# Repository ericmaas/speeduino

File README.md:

## NO2C vDD

All Credit to the Speeduino Team
https://github.com/speeduino/speeduino

And 

https://github.com/turboedge/SpeedyBoards/

Originally forked from:
https://github.com/turboedge/SpeedyBoards/tree/master

Wideband ideation from:
https://github.com/oelprinz-org

Please review my workprior to printing, and test your work. 

I am not an engineer, mechanic, or automotive specialist, please use at your own risk.

Please review vehicle laws and regulations prior to use. 

Connector used is a TE # 3-6437285-0

Future Feature Wish List:

- SD Card for data logging
- Dedicated prototyping pins (would be great for oil pressure)

The No Overhang Two Channel was designed to incorporate as many features as possible into a SMD board that moves to a new smaller format size. Microcontroller onboard. It is a 2+2 channel board that incorporates the features below.
- Two injector channels
- Two ignitor channels
- Outputs for VVT PWM idle, boost, fuel pump, and tachometer
- Two trigger inputs
- Launch input
- Analog inputs for CLT, IAT, TPS, and O2
- MAP sensor onboard
- Socket for stepper idle control module
- Additional pins for i2c and canbus
- LSU 4.9 Wideband integration
- Bluetooth 4.0 (HM-10)

Latest version: DD3

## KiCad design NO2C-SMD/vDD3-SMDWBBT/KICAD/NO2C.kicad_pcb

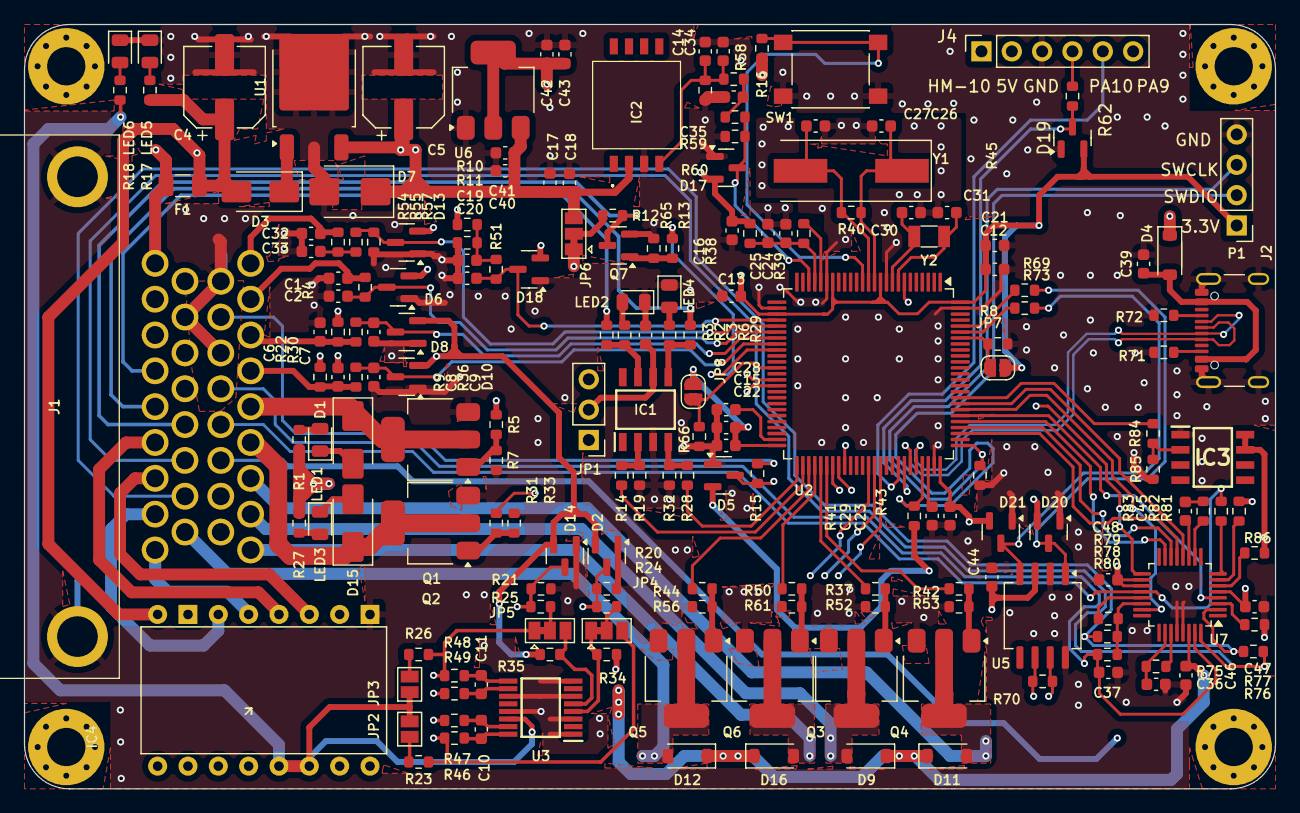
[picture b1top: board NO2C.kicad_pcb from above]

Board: 4 copper layers, 104.8 x 64.0 mm, 188 parts (0 on the bottom side), 136 nets.

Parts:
C1, C3, C6, C8, C13, C15, C16, C17, C18, C19, C21, C22, C23, C25, C28, C29, C32, C34, C36, C40, C43, C44, C45, C46, C47, C48: 100nF; C_0603_1608Metric
C2, C7, C9, C20, C33, C35: 220nF; C_0603_1608Metric
C4, C5: 47u 50v; CP_Elec_6.3x7.7
C10, C11, C12, C24: 1nF; C_0603_1608Metric
C14: 47pF; C_0603_1608Metric
C26, C27: 22pF; C_0603_1608Metric
C30, C31: 12pF; C_0603_1608Metric
C37: 2.2nF; C_0603_1608Metric
C39, C41, C42: 10uF; C_0603_1608Metric
D1, D15: 1N4004; D_SMA
D2, D5, D6, D8, D10, D13, D14, D17, D18, D19, D20, D21: BAT54S; SOT-23
D3: 60V 1A; D_SMA
D4, D9, D11, D12, D16: 1N4007-A7; D_SOD-123
D7: 1SMB5919BT3G; D_SMB
F1: 1A 60V; Fuse_1206_3216Metric
IC1: TC4424AVOA; SOIC127P600X175-8N
IC2: MPXH6400AC6T1
IC3: VNS3NV04DPTR-E; SOIC127P600X175-8N
IC4: CONN_02X08; DRV8825
J1: 3-6437285-0; 364372850
J2: USB_C_Receptacle_USB2.0_16P; USB_C_Receptacle_GCT_USB4105-xx-A_16P_TopMnt_Horizontal
J4: HM-10; PinSocket_1x06_P2.54mm_Vertical
JP1: ING-VLT; PinHeader_1x03_P2.54mm_Vertical
JP2, JP3: Jumper_NO_Small; SolderJumper-2_P1.3mm_Open_Pad1.0x1.5mm
JP4, JP5, JP6: SolderJumper_3_Bridged12; SolderJumper-3_P1.3mm_Bridged12_Pad1.0x1.5mm
JP7, JP8: Jumper_2_Open; SolderJumper-2_P1.3mm_Open_RoundedPad1.0x1.5mm
LED1, LED2, LED3, LED4, LED5, LED6: RED; LED_0805_2012Metric
P1: Conn_01x04; PinHeader_1x04_P2.54mm_Vertical
Q1, Q2, Q3, Q4, Q5, Q6: BSP78HUMA1; SOT-223-3_TabPin2
Q7: AO3400A; SOT-23
R1, R2, R6, R27: 2K; R_0603_1608Metric
R3, R29: 47R; R_0603_1608Metric
R4, R18, R24, R25, R30, R36, R51, R54, R58, R62: 470R; R_0603_1608Metric
R5, R13, R31, R37, R42, R44, R50: 100R; R_0603_1608Metric
R7, R8, R16, R20, R21, R33, R41, R43, R46, R47, R48, R49, R52, R53, R56, R61, R65, R66, R77, R81, R82, R83: 10K; R_0603_1608Metric
R9, R22: 2K49; R_0603_1608Metric
R10: 33K; R_0603_1608Metric
R11, R45: 51K; R_0603_1608Metric
R12, R14, R15, R23, R26, R28, R34, R35, R69, R73: 1K; R_0603_1608Metric
R17: 2K7; R_0603_1608Metric
R19, R32, R75, R80, R85: 100K; R_0603_1608Metric
R38, R39: 0R; R_0603_1608Metric
R40: 1M; R_0603_1608Metric
R55, R59: 4K7; R_0603_1608Metric
R57, R60: 9K1; R_0603_1608Metric
R70: 120R; R_0603_1608Metric
R71, R72: 5.1K; R_0603_1608Metric
R76: 61.9R; R_0603_1608Metric
R78: 470K; R_0603_1608Metric
R79, R84: 4.7K; R_0603_1608Metric
R86: 6.8K; R_0603_1608Metric
SW1: SW_Push; SW_Push_1P1T_NO_6x6mm_H9.5mm
U1: L7805CDT(UMW); TO-252-2
U2: STM32F407VETx; LQFP-100_14x14mm_P0.5mm
U3: MAX9926UAEE+; SOP64P602X175-16N
U5: TJA1050; SO-8_5.3x6.2mm_P1.27mm
U6: AMS1117-3.3; SOT-223-3_TabPin2
U7: CJ125_32; LQFP-32_5x5mm_P0.5mm
Y1: 8Mhz; Crystal_SMD_HC49-SD
Y2: 32.768Khz; Crystal_SMD_3215-2Pin_3.2x1.5mm

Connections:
+3.3V: C12.2, C13.2, C15.2, C16.2, C21.2, C22.2, C23.2, C42.1, C43.1, D2.2 (C2), D5.2 (K), D6.2 (K), D8.2 (K), D10.2 (K), D13.2 (K), D14.2 (C2), D17.2 (K), D18.2 (K), D19.2 (K), D20.2 (K), D21.2 (K), JP7.2 (B), JP8.2 (B), P1.1, R9.1, R16.1, R22.1, R34.2, R35.2, R38.2, R41.1, U2.11 (VDD), U2.19 (VDD), U2.28 (VDD), U2.50 (VDD), U2.75 (VDD), U2.100 (VDD), U6.2 (VO)
+5V: C5.1, C17.1, C18.1, C40.1, C41.1, C44.1, C47.2, C48.2, D4.1 (K), D7.1 (K), IC2.2 (_VS), IC4.5, IC4.6, J1.10, J4.2, JP1.1, JP2.2, JP3.2, JP6.3 (B), R18.1, R81.1, U1.3 (OUT), U3.14 (VCC), U5.3 (vcc), U6.3 (VI), U7.5 (VCCS), U7.18 (VCCSS), U7.19 (VCC)
+12V: C4.1, C46.2, D3.2 (A), D9.1 (K), D11.1 (K), D12.1 (K), D16.1 (K), F1.1, IC4.16, JP1.3, JP6.1 (A), R1.2, R17.2, R27.2, U7.30 (UB)
+BATT: F1.2, J1.1, R10.1
/BOOST: D9.2 (A), J1.33, Q3.2 (D)
/BOOT0: JP7.1 (A), R8.2, U2.94 (BOOT0)
/BOOT1: JP8.1 (A), R66.1, U2.37 (PB2)
/CLT: C6.1, J1.28, R22.2, R30.1
/DIAHG: U2.81 (PD0), U7.4 (DIAHG)
/DIR: IC4.8, U2.65 (PC8)
/ENBL: IC4.1, U2.63 (PC6)
/FUELP: D16.2 (A), J1.34, Q6.2 (D)
/HEAT_OUT-: R84.1, U2.84 (PD3)
/IAT: C8.1, J1.29, R9.2, R36.1
/IDLE: D12.2 (A), J1.17, Q5.2 (D)
/IGN1: J1.4, R3.2
/IGN2: J1.5, R29.2
/INJ1: D1.1 (K), J1.30, Q1.2 (D)
/INJ2: D15.1 (K), J1.31, Q2.2 (D)
/LAUNCH: J1.19, R15.2
/O2: C32.1, J1.26, R54.1
/PA0: D17.3 (COM), R59.2, R60.2, U2.23 (PA0)
/PA1: C20.1, D18.3 (COM), R51.2, U2.29 (PA4)
/PA2: D13.3 (COM), R55.2, R57.2, U2.30 (PA5)
/PA3: C2.1, D6.3 (COM), R4.2, U2.31 (PA6)
/PA4: C7.1, D8.3 (COM), R30.2, U2.32 (PA7)
/PA5: C9.1, D10.3 (COM), R36.2, U2.33 (PC4)
/PA9: J4.5, U2.68 (PA9)
/PA10: D19.3 (COM), R62.1, U2.69 (PA10)
/PB8: R73.1, U2.95 (PB8)
/PB9: R69.1, U2.96 (PB9)
/PD4: R50.2, U2.54 (PB15)
/PD5: R44.2, U2.53 (PB14)
/PD6: R42.2, U2.56 (PD9)
/PD7: R37.2, U2.55 (PD8)
/PD8: R5.2, U2.39 (PE8)
/PD9: R31.2, U2.40 (PE9)
/PD10: D14.3 (C1A2), R21.1, R25.1, U2.57 (PD10)
/PD11: D2.3 (C1A2), R20.1, R24.1, U2.58 (PD11)
/PD12: R28.2, U2.51 (PB12)
/PD13: R14.2, U2.52 (PB13)
/PD14: R13.1, U2.34 (PC5)
/SPI3_MISO: U2.79 (PC11), U7.14 (MISO)
/SPI3_MOSI: U2.80 (PC12), U7.15 (MOSI)
/SPI3_SCK: U2.78 (PC10), U7.13 (SCK)
/SS3: U2.7 (PC13), U7.17 (SS)
/STEP: IC4.7, U2.64 (PC7)
/STP-A1: IC4.12, J1.6
/STP-A2: IC4.11, J1.7
/STP-B1: IC4.13, J1.9
/STP-B2: IC4.14, J1.8
/SWCLK: P1.3, R43.1, U2.76 (PA14)
/SWDIO: P1.2, R41.2, U2.72 (PA13)
/TACHO: J1.14, Q7.3 (D), R12.1
/TPS: C1.1, J1.27, R4.1
/UA: U2.82 (PD1), U7.23 (UA)
/UR: U2.83 (PD2), U7.12 (UR)
/USB_D+: J2.A6 (D+), J2.B6 (D+), U2.71 (PA12)
/USB_D-: J2.A7 (D-), J2.B7 (D-), U2.70 (PA11)
/VR1-: J1.3, R47.1
/VR2-: J1.12, R49.1
/VVT: D11.2 (A), J1.32, Q4.2 (D)
CANH: J1.24, R70.2, U5.7 (CANH)
CANL: J1.25, R70.1, U5.6 (CANL)
DIAHD: R86.1, U7.6 (DIAHD)
GND: C1.2, C2.2, C3.2, C4.2, C5.2, C6.2, C7.2, C8.2, C9.2, C12.1, C13.1, C14.2, C15.1, C16.1, C17.2, C18.2, C19.2, C20.2, C21.1, C22.1, C23.1, C24.1, C25.1, C26.1, C27.1, C28.1, C29.1, C30.1, C31.1, C32.2, C33.2, C34.2, C35.2, C36.2, C37.1, C39.2, C40.2, C41.2, C42.2, C43.2, C44.2, C46.1, C47.1, C48.1, D2.1 (A1), D5.1 (A), D6.1 (A), D7.2 (A), D8.1 (A), D10.1 (A), D13.1 (A), D14.1 (A1), D17.1 (A), D18.1 (A), D19.1 (A), D20.1 (A), D21.1 (A), IC1.3 (GND), IC2.3 (GND), IC3.1 (SOURCE1), IC4.9, J1.11, J1.18, J1.20, J1.MH1, J1.MH2, J2.A1 (GND), J2.A12 (GND), J2.B1 (GND), J2.B12 (GND), J2.S1 (SHIELD), J4.3, LED2.1 (K), LED4.1 (K), LED5.1 (K), LED6.1 (K), P1.4, Q1.3 (S), Q2.3 (S), Q3.3 (S), Q4.3 (S), Q5.3 (S), Q6.3 (S), Q7.2 (S), R7.2, R8.1, R11.2, R19.2, R20.2, R21.2, R32.2, R33.2, R43.2, R45.2, R52.2, R53.2, R56.2, R57.1, R60.1, R61.2, R65.2, R66.2, R71.2, R72.2, R77.1, R85.1, SW1.1, U1.2 (GND), U2.10 (VSS), U2.20 (VSSA), U2.27 (VSS), U2.74 (VSS), U2.99 (VSS), U3.1 (INT_THRS1), U3.3 (BIAS1), U3.6 (BIAS2), U3.8 (INT_THRS2), U3.11 (GND), U3.13 (ZERO_EN), U5.2 (gnd), U5.8 (S), U6.1 (GND), U7.28 (GNDS), U7.29 (GND)
HEAT-: IC3.7 (DRAIN1_1), IC3.8 (DRAIN1_2), J1.23, R86.2
IA: J1.16, R76.1, R78.2, U7.2 (IA)
IP: J1.15, R76.2, U7.32 (IP)
unnamed: C19.1, R10.2, R11.1, R51.1
unnamed: C33.1, R54.2, R55.1
unnamed: C35.1, R58.2, R59.1
unnamed: C45.1, R83.2
unnamed: D1.2 (A), LED1.1 (K)
unnamed: D3.1 (K), U1.1 (IN)
unnamed: D5.3 (COM), R15.1, U2.59 (PD12)
unnamed: D15.2 (A), LED3.1 (K)
unnamed: D20.3 (COM), R69.2, U5.1 (txd)
unnamed: D21.3 (COM), R73.2, U5.4 (rxd)
unnamed: IC1.2 (INA), R14.1, R19.1
unnamed: IC1.4 (INB), R28.1, R32.1
unnamed: IC1.7 (OUTA), R2.1, R3.1
unnamed: IC1.5 (OUTB), R6.1, R29.1
unnamed: C3.1, IC1.6 (VDD), JP1.2
unnamed: C14.1, C34.1, IC2.4 (VOUT), R45.1, R58.1
unnamed: IC3.2 (INPUT_1), R84.2, R85.2
unnamed: J2.A8 (SBU1), R72.1
unnamed: J2.B8 (SBU2), R71.1
unnamed: J4.4, R62.2
unnamed: JP2.1, R23.2
unnamed: JP3.1, R26.2
unnamed: JP4.1 (A), R34.1, U3.4 (COUT1)
unnamed: JP4.2 (C), R24.2
unnamed: JP5.3 (B), R35.1, U3.5 (COUT2)
unnamed: JP5.2 (C), R25.2
unnamed: JP6.2 (C), R12.2
unnamed: LED1.2 (A), R1.1
unnamed: LED2.2 (A), R2.2
unnamed: LED3.2 (A), R27.1
unnamed: LED4.2 (A), R6.2
unnamed: LED5.2 (A), R17.1
unnamed: LED6.2 (A), R18.2
unnamed: Q1.1 (G), R5.1, R7.1
unnamed: Q2.1 (G), R31.1, R33.1
unnamed: Q3.1 (G), R37.1, R52.1
unnamed: Q4.1 (G), R42.1, R53.1
unnamed: Q5.1 (G), R44.1, R56.1
unnamed: Q6.1 (G), R50.1, R61.1
unnamed: Q7.1 (G), R13.2, R65.1
unnamed: R16.2, SW1.2, U2.14 (NRST)
unnamed: C31.2, U2.8 (PC14), Y2.2
unnamed: C30.2, U2.9 (PC15), Y2.1
unnamed: C26.2, R40.1, U2.12 (PH0), Y1.1
unnamed: C27.2, R40.2, U2.13 (PH1), Y1.2
unnamed: C28.2, U2.49 (VCAP_1)
unnamed: C29.2, U2.73 (VCAP_2)
unnamed: R39.2, U2.21 (VREF+)
unnamed: C10.2, R46.2, U3.16 (IN1+)
unnamed: C10.1, R47.2, U3.15 (IN1-)
unnamed: C11.2, R48.2, U3.9 (IN2+)
unnamed: C11.1, R49.2, U3.10 (IN2-)
unnamed: C36.1, R75.2, U7.26 (CF)
unnamed: C45.2, U7.11 (CM)
unnamed: R77.2, U7.3 (OSZ)
unnamed: R75.1, U7.27 (RF)
unnamed: R83.1, U7.10 (RM)
unnamed: R82.2, U7.8 (RS)
unnamed: R81.2, U7.7 (RST)
unnamed: R78.1, R79.2, R80.1, U7.22 (UP)
unnamed: R79.1, U7.21 (US)
UN: C37.2, J1.21, R80.2, U7.31 (UN)
VBUS: C39.1, D4.2 (A), J2.A4 (VBUS), J2.A9 (VBUS), J2.B4 (VBUS), J2.B9 (VBUS)
VDA: C24.2, C25.2, R38.1, R39.1, U2.22 (VDDA)
VM: J1.22, R82.1, U7.20 (VM)
VR1+: J1.2, JP4.3 (B), R23.1, R46.1
VR2+: J1.13, JP5.1 (A), R26.1, R48.1

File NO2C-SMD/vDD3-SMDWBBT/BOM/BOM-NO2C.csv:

Comment,Designator,Footprint,LCSC,Quantity
22pF,"C26,C27",C_0603_1608Metric,C105620,2
47pF,C14,C_0603_1608Metric,C105622,1
12pF,"C30,C31",C_0603_1608Metric,C107034,2
220nF,"C2,C20,C33,C35,C7,C9",C_0603_1608Metric,C107083,6
10uF,"C39,C41,C42",C_0603_1608Metric,C109457,3
8Mhz,Y1,Crystal_SMD_HC49-SD,C12674,1
2K7,R17,R_0603_1608Metric,C13167,1
60V 1A,D3,D_SMA,C134421,1
100nF,"C1,C13,C15,C16,C17,C18,C19,C21,C22,C23,C25,C28,C29,C3,C32,C34,C36,C40,C43,C44,C45,C46,C47,C48,C6,C8",C_0603_1608Metric,C14663,26
MAX9926UAEE+,U3,SOP64P602X175-16N,C1523548,1
1A 60V,F1,Fuse_1206_3216Metric,C163133,1
1nF,"C10,C11,C12,C24",C_0603_1608Metric,C1636,4
USB_C_Receptacle_USB2.0_16P,J2,USB_C_Receptacle_GCT_USB4105-xx-A_16P_TopMnt_Horizontal,C165948,1
CJ125_32,U7,LQFP-32_5x5mm_P0.5mm,C18198890,1
0R,"R38,R39",R_0603_1608Metric,C21189,2
1K,"R12,R14,R15,R23,R26,R28,R34,R35,R69,R73",R_0603_1608Metric,C21190,10
100R,"R13,R31,R37,R42,R44,R5,R50",R_0603_1608Metric,C22775,7
120R,R70,R_0603_1608Metric,C22787,1
2K49,"R22,R9",R_0603_1608Metric,C22908,2
1M,R40,R_0603_1608Metric,C22935,1
2K,"R1,R2,R27,R6",R_0603_1608Metric,C22975,4
61.9R,R76,R_0603_1608Metric,C23092,1
4K7,"R55,R59",R_0603_1608Metric,C23162,2
470R,"R18,R24,R25,R30,R36,R4,R51,R54,R58,R62",R_0603_1608Metric,C23179,10
47R,"R29,R3",R_0603_1608Metric,C23182,2
5.1K,"R71,R72",R_0603_1608Metric,C23186,2
51K,"R11,R45",R_0603_1608Metric,C23196,2
9K1,"R57,R60",R_0603_1608Metric,C23260,2
100K,"R19,R32,R75,R80,R85",R_0603_1608Metric,C25803,5
10K,"R16,R20,R21,R33,R41,R43,R46,R47,R48,R49,R52,R53,R56,R61,R65,R66,R7,R77,R8,R81,R82,R83",R_0603_1608Metric,C25804,22
6.8K,R86,R_0603_1608Metric,C26004,1
BSP78HUMA1,"Q1,Q2,Q3,Q4,Q5,Q6",SOT-223-3_TabPin2,C2653794,6
MPXH6400AC6T1,IC2,MPXH6400AC6T1,C2828031,1
STM32F407VETx,U2,LQFP-100_14x14mm_P0.5mm,C28730,1
1N4007-A7,"D11,D12,D16,D4,D9",D_SOD-123,C2902912,5
2.2nF,C37,C_0603_1608Metric,C309517,1
32.768Khz,Y2,Crystal_SMD_3215-2Pin_3.2x1.5mm,C32346,1
47u 50v,"C4,C5",CP_Elec_6.3x7.7,C3349,2
AO3400A,Q7,SOT-23,C344010,1
470K,R78,R_0603_1608Metric,C365173,1
HM-10,J4,PinSocket_1x06_P2.54mm_Vertical,C40877,1
33K,R10,R_0603_1608Metric,C4216,1
TC4424AVOA,IC1,SOIC127P600X175-8N,C44150,1
BAT54S,"D10,D13,D14,D17,D18,D19,D2,D20,D21,D5,D6,D8",SOT-23,C47546,12
ING-VLT,JP1,PinHeader_1x03_P2.54mm_Vertical,C49257,1
VNS3NV04DPTR-E,IC3,SOIC127P600X175-8N,C503069,1
Conn_01x04,P1,PinHeader_1x04_P2.54mm_Vertical,C5116483,1
SW_Push,SW1,SW_Push_1P1T_NO_6x6mm_H9.5mm,C5127964,1
AMS1117-3.3,U6,SOT-223-3_TabPin2,C6186,1
TJA1050,U5,SO-8_5.3x6.2mm_P1.27mm,C6952,1
1N4004,"D1,D15",D_SMA,C727080,2
L7805CDT(UMW),U1,TO-252-2,C7394043,1
1SMB5919BT3G,D7,D_SMB,C7422622,1
RED,"LED1,LED2,LED3,LED4,LED5,LED6",LED_0805_2012Metric,C84256,6
4.7K,"R79,R84",R_0603_1608Metric,C99782,2
3-6437285-0,J1,364372850,,1

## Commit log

2024-10-30 Draft DD
2024-10-30 quick parts supply update
2024-10-30 read me update
2024-10-31 step file added
2024-10-31 step file update
2024-10-31 Clean Up
2024-10-31 clean up
    Removed older and duplicate files. Added Step File in a zip
2024-10-31 Updated readme
    Wish list added to readme.
2024-11-18 Updated with WB
    LSU 4.9 wideband integration
2024-11-18 Wideband file clean up
    Organized file structure and general updates and cleaned.
2024-11-23 plugin wideband
    Added wide band to the main connector.
2024-11-23 Wideband integrated
    Cleaned up file structure and included wide band upload
2024-11-23 Readme Update
    Information related to wide band, credit where due, and versioning.
2025-01-12 Bluetooth added
2025-01-12 bluetooth
2025-01-12 Bluetooth
    Added
2025-01-12 updated readme file
